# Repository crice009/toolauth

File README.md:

# toolauth

A simple server to handle integration of a tool authorization system with custom curcuit boards. 
Designed by and for use at MakeHaven in New Haven, CT.

## toolauth-hardware
The hardware is also custom. It can be referenced [here](https://github.com/crice009/toolauth-hardware).

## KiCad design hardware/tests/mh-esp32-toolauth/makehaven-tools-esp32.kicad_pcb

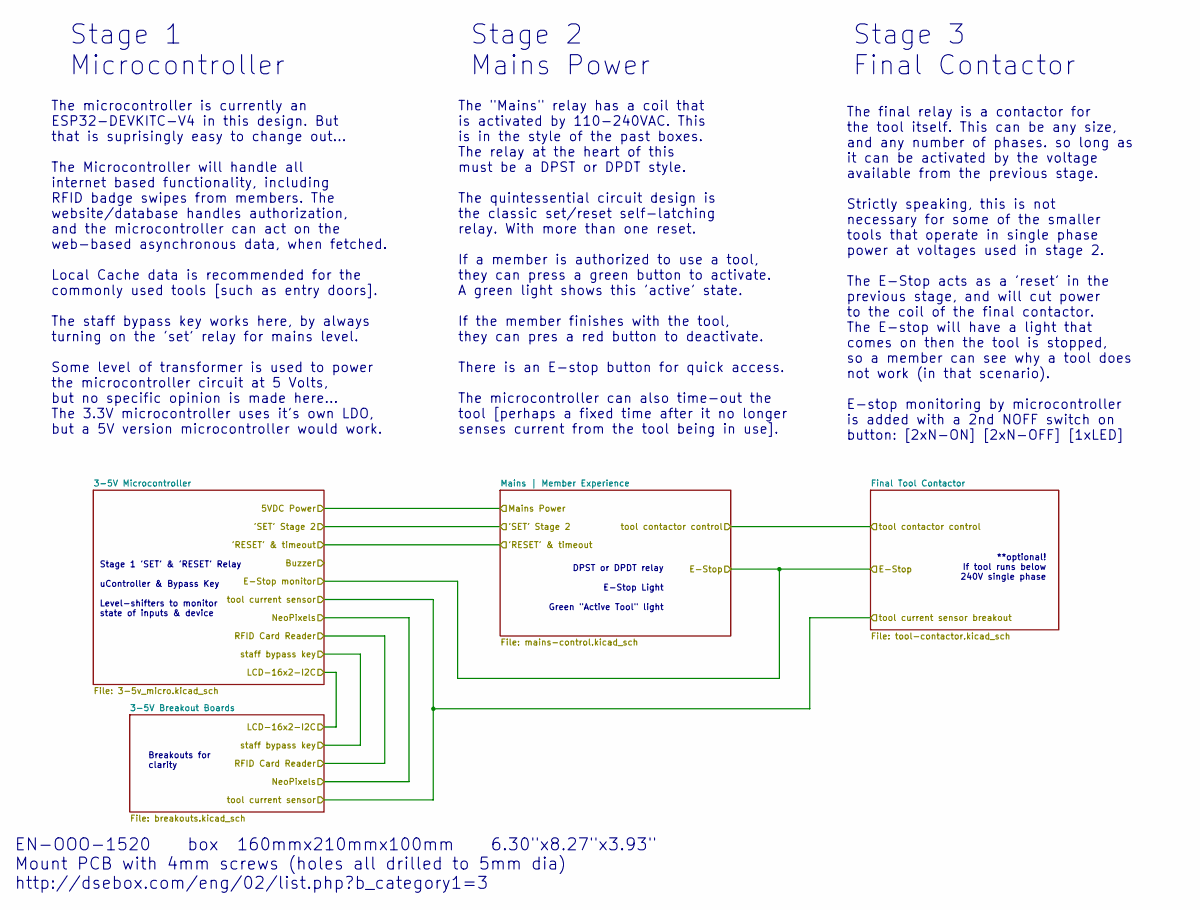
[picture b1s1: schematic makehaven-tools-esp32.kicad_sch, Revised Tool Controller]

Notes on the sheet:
Stage 3 Final Contactor
Stage 1 'SET' & 'RESET' Relay uController & Bypass Key Level-shifters to monitor state of inputs & device
The final relay is a contactor for the tool itself. This can be any size, and any number of phases. so long as it can be activated by the voltage available from the previous stage. Strictly speaking, this is not necessary for some of the smaller tools that operate in single phase power at voltages 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
Stage 2 Mains Power
Stage 1 Microcontroller
The "Mains" relay has a coil that is activated by 110-240VAC. This is in the style of the past boxes. The relay at the heart of this must be a DPST or DPDT style. The quintessential circuit design is the classic set/reset self-latching relay. With more than one reset. If a member is authorized to u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
**optional! If tool runs below 240V single phase
Breakouts for clarity
The microcontroller is currently an ESP32-DEVKITC-V4 in this design. But that is suprisingly easy to change out... The Microcontroller will handle all internet based functionality, including RFID badge swipes from members. The website/database handles authorization, and the microcontroller can act 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
DPST or DPDT relay E-Stop Light Green "Active Tool" light
EN-OOO-1520 box 160mmx210mmx100mm 6.30"x8.27"x3.93" Mount PCB with 4mm screws (holes all drilled to 5mm dia) http://dsebox.com/eng/02/list.php?b_category1=3

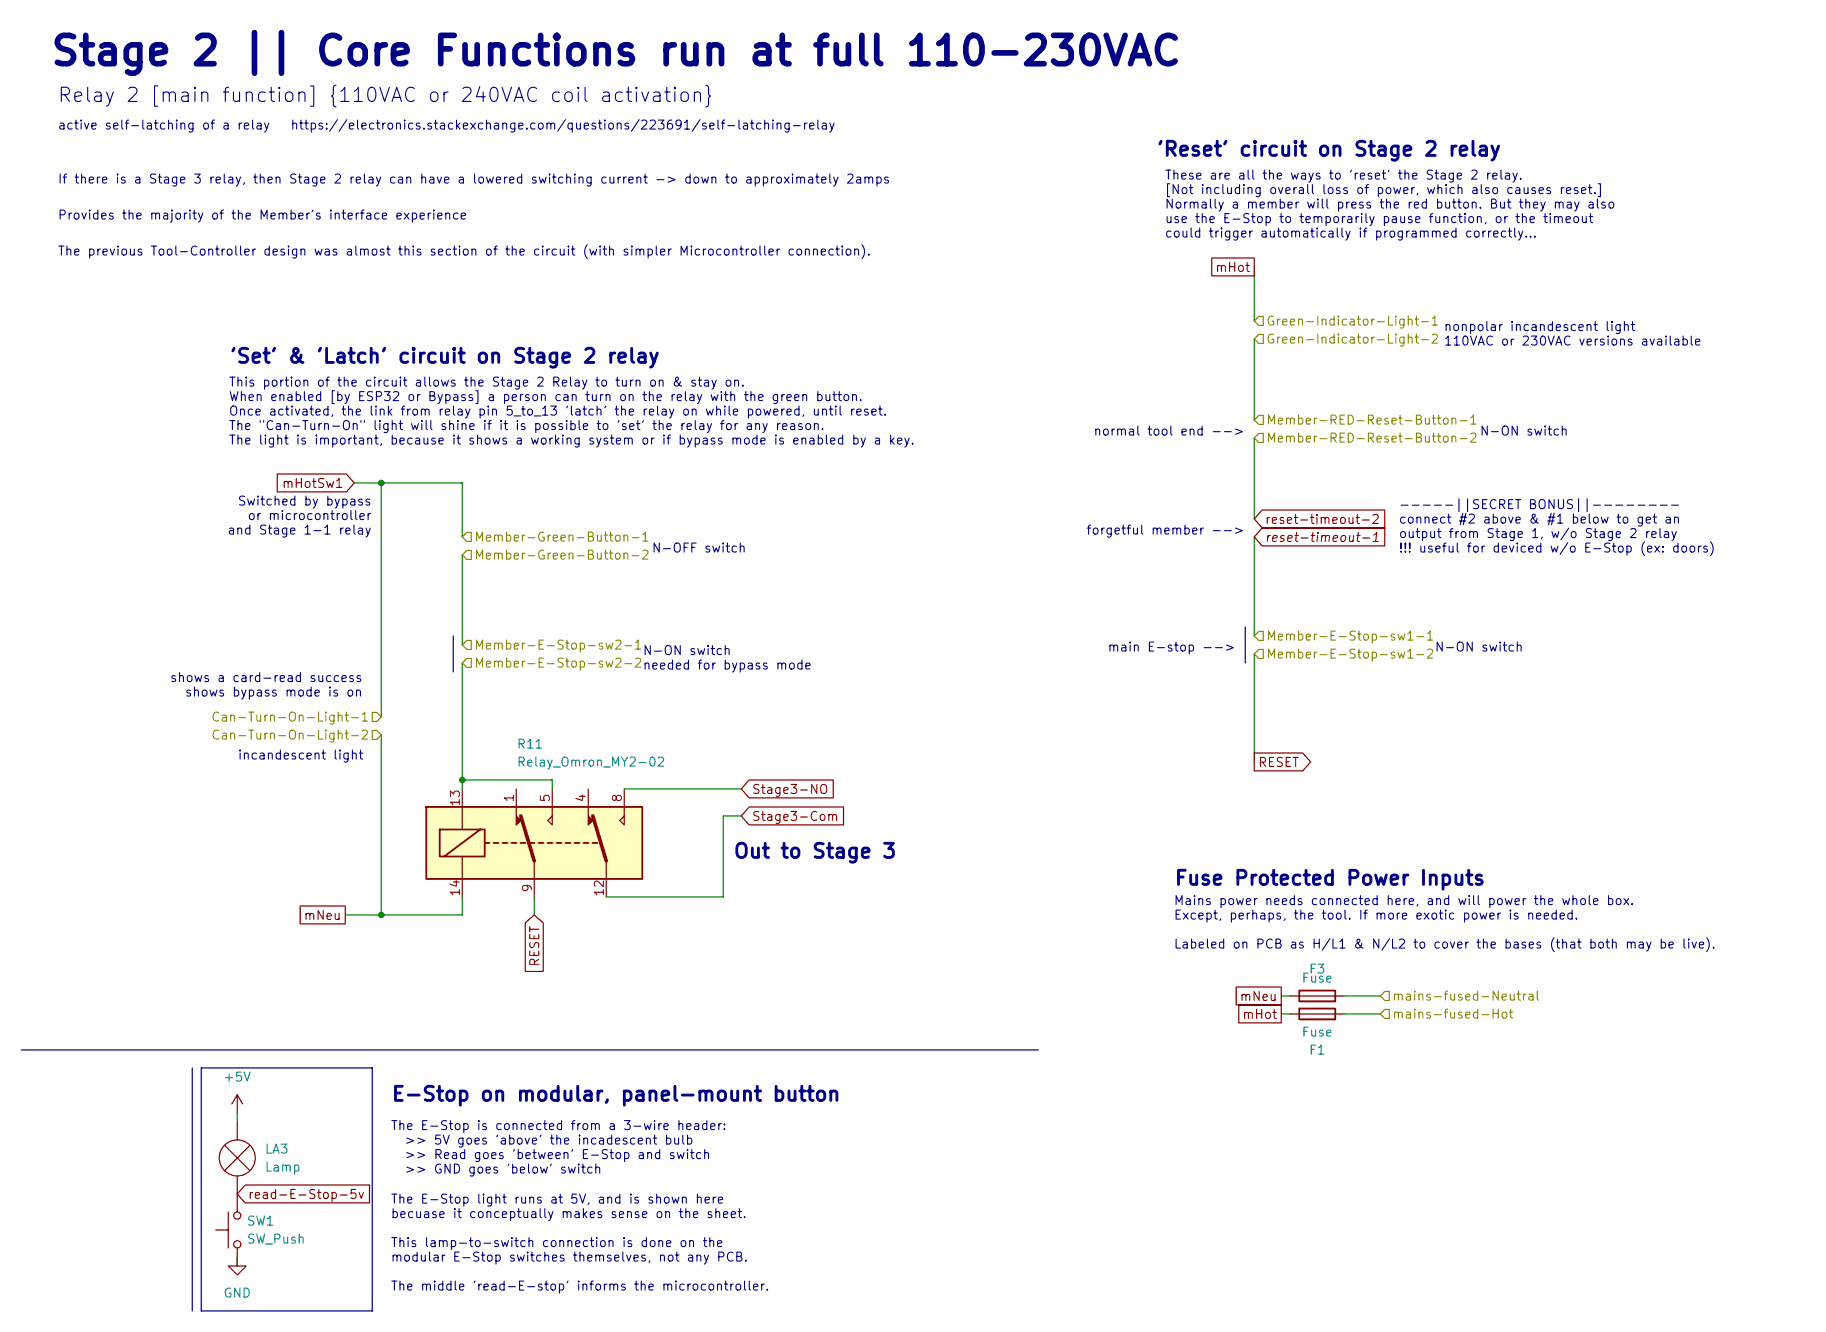
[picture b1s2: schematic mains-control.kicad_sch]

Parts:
F1, F3: Fuse; Fuseholder_Littelfuse_100_series_5x20mm
LA3: Lamp
R11: Relay_Omron_MY2-02; relay-Omron-MY2-02
SW1: SW_Push

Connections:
/Mains | Member Experience/Member-E-Stop-sw2-2: R11.5, R11.13; also elsewhere on the board
/Mains | Member Experience/mains-fused-Hot: F1.2; also elsewhere on the board
/Mains | Member Experience/mains-fused-Neutral: F3.2; also elsewhere on the board
unnamed: LA3.1 (-), SW1.2
RESET: R11.9; also elsewhere on the board
Stage3-Com: R11.12; also elsewhere on the board
mNeu: F3.1, R11.14; also elsewhere on the board

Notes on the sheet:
shows a card-read success shows bypass mode is on
'Set' & 'Latch' circuit on Stage 2 relay
Out to Stage 3
E-Stop on modular, panel-mount button
N-ON switch needed for bypass mode
This portion of the circuit allows the Stage 2 Relay to turn on & stay on. When enabled [by ESP32 or Bypass] a person can turn on the relay with the green button. Once activated, the link from relay pin 5_to_13 'latch' the relay on while powered, until reset. The "Can-Turn-On" light will shine if i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
incandescent light
N-ON switch
The previous Tool-Controller design was almost this section of the circuit (with simpler Microcontroller connection).
-----||SECRET BONUS||-------- connect #2 above & #1 below to get an output from Stage 1, w/o Stage 2 relay !!! useful for deviced w/o E-Stop (ex: doors)
Provides the majority of the Member's interface experience
active self-latching of a relay https://electronics.stackexchange.com/questions/223691/self-latching-relay
N-OFF switch
normal tool end -->
If there is a Stage 3 relay, then Stage 2 relay can have a lowered switching current -> down to approximately 2amps
These are all the ways to 'reset' the Stage 2 relay. [Not including overall loss of power, which also causes reset.] Normally a member will press the red button. But they may also use the E-Stop to temporarily pause function, or the timeout could trigger automatically if programmed correctly...
forgetful member -->
Mains power needs connected here, and will power the whole box. Except, perhaps, the tool. If more exotic power is needed. Labeled on PCB as H/L1 & N/L2 to cover the bases (that both may be live).
The E-Stop is connected from a 3-wire header: >> 5V goes 'above' the incadescent bulb >> Read goes 'between' E-Stop and switch >> GND goes 'below' switch
Relay 2 [main function] {110VAC or 240VAC coil activation}
'Reset' circuit on Stage 2 relay
The E-Stop light runs at 5V, and is shown here becuase it conceptually makes sense on the sheet. This lamp-to-switch connection is done on the modular E-Stop switches themselves, not any PCB. The middle 'read-E-stop' informs the microcontroller.
Switched by bypass or microcontroller and Stage 1-1 relay
main E-stop -->
Fuse Protected Power Inputs
nonpolar incandescent light 110VAC or 230VAC versions available
Stage 2 || Core Functions run at full 110-230VAC

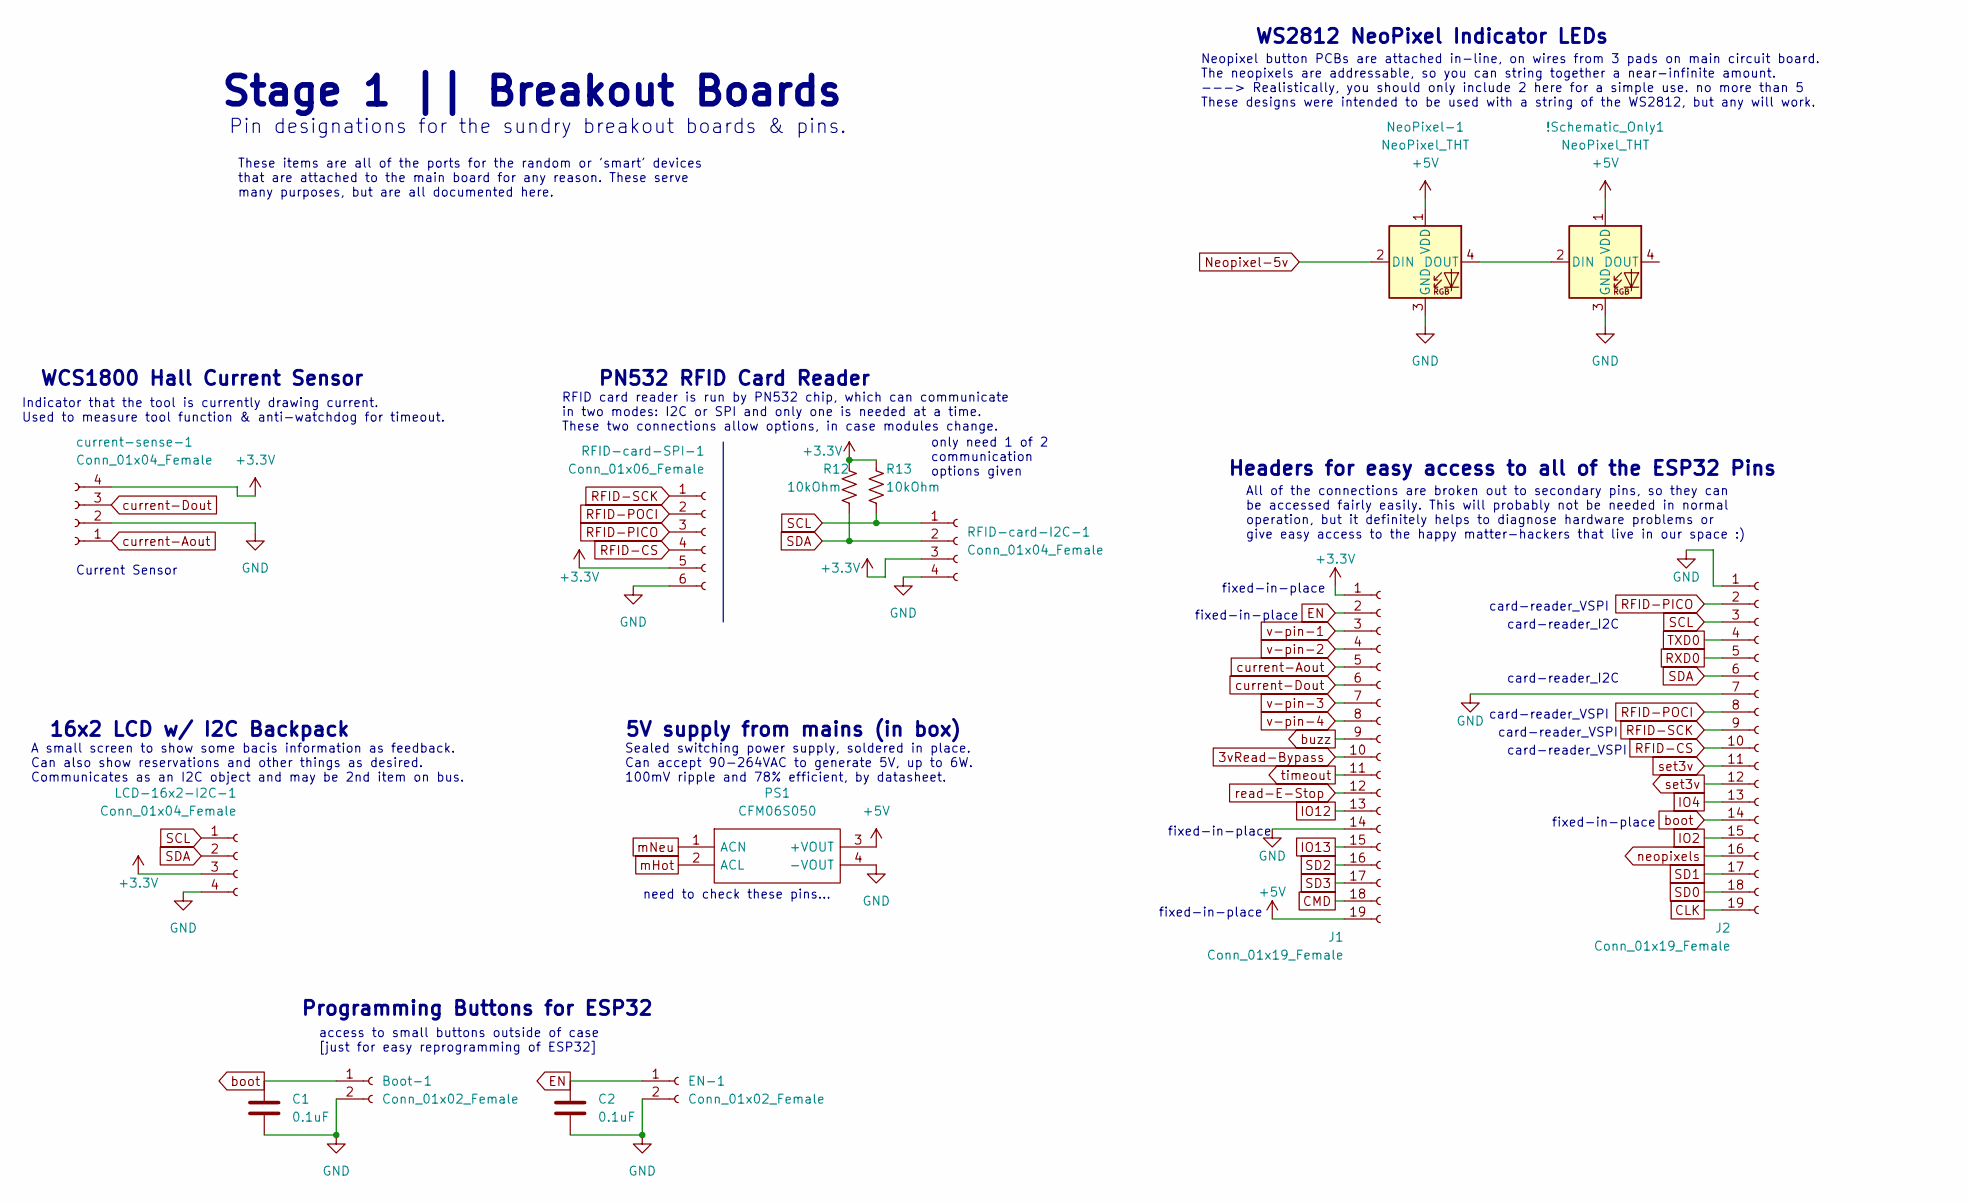
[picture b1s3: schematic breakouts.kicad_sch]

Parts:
!Schematic_Only1: NeoPixel_THT
Boot-1: Conn_01x02_Female; PinSocket_1x02_P2.54mm_Vertical
C1, C2: 0.1uF; C_1206_3216Metric_Pad1.33x1.80mm_HandSolder
EN-1: Conn_01x02_Female; PinSocket_1x02_P2.54mm_Vertical
J1, J2: Conn_01x19_Female; PinSocket_1x19_P2.54mm_Vertical
LCD-16x2-I2C-1: Conn_01x04_Female; PinSocket_1x04_P2.54mm_Vertical
NeoPixel-1: NeoPixel_THT; PinSocket_1x03_P2.54mm_Vertical
PS1: CFM06S050; Mouser Part Number 418-CFM06S050
R12, R13: 10kOhm; R_1206_3216Metric_Pad1.30x1.75mm_HandSolder
RFID-card-I2C-1: Conn_01x04_Female; PinSocket_1x04_P2.54mm_Vertical
RFID-card-SPI-1: Conn_01x06_Female; PinSocket_1x06_P2.54mm_Vertical
current-sense-1: Conn_01x04_Female; PinSocket_1x04_P2.54mm_Vertical

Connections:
3vRead-Bypass: J1.10; also elsewhere on the board
+3V3: J1.1, LCD-16x2-I2C-1.3, R12.2, R13.2, RFID-card-I2C-1.3, RFID-card-SPI-1.5, current-sense-1.4; also elsewhere on the board
+5V: !Schematic_Only1.1 (VDD), J1.19, NeoPixel-1.1 (VDD), PS1.3 (+VOUT); also elsewhere on the board
CLK: J2.19; also elsewhere on the board
CMD: J1.18; also elsewhere on the board
EN: C2.1, EN-1.1, J1.2; also elsewhere on the board
GND: !Schematic_Only1.3 (GND), Boot-1.2, C1.2, C2.2, EN-1.2, J1.14, J2.1, J2.7, LCD-16x2-I2C-1.4, NeoPixel-1.3 (GND), PS1.4 (-VOUT), RFID-card-I2C-1.4, RFID-card-SPI-1.6, current-sense-1.2; also elsewhere on the board
IO2: J2.15; also elsewhere on the board
IO4: J2.13; also elsewhere on the board
IO12: J1.13; also elsewhere on the board
IO13: J1.15; also elsewhere on the board
Neopixel-5v: NeoPixel-1.2 (DIN); also elsewhere on the board
unnamed: !Schematic_Only1.2 (DIN), NeoPixel-1.4 (DOUT)
RFID-CS: J2.10, RFID-card-SPI-1.4; also elsewhere on the board
RFID-PICO: J2.2, RFID-card-SPI-1.3; also elsewhere on the board
RFID-POCI: J2.8, RFID-card-SPI-1.2; also elsewhere on the board
RFID-SCK: J2.9, RFID-card-SPI-1.1; also elsewhere on the board
RXD0: J2.5; also elsewhere on the board
SCL: J2.3, LCD-16x2-I2C-1.1, R13.1, RFID-card-I2C-1.1; also elsewhere on the board
SD0: J2.18; also elsewhere on the board
SD1: J2.17; also elsewhere on the board
SD2: J1.16; also elsewhere on the board
SD3: J1.17; also elsewhere on the board
SDA: J2.6, LCD-16x2-I2C-1.2, R12.1, RFID-card-I2C-1.2; also elsewhere on the board
TXD0: J2.4; also elsewhere on the board
boot: Boot-1.1, C1.1, J2.14; also elsewhere on the board
buzz: J1.9; also elsewhere on the board
current-Aout: J1.5, current-sense-1.1; also elsewhere on the board
current-Dout: J1.6, current-sense-1.3; also elsewhere on the board
mNeu: PS1.1 (ACN); also elsewhere on the board
neopixels: J2.16; also elsewhere on the board
read-E-Stop: J1.12; also elsewhere on the board
set3v: J2.11, J2.12; also elsewhere on the board
timeout: J1.11; also elsewhere on the board
v-pin-1: J1.3; also elsewhere on the board
v-pin-2: J1.4; also elsewhere on the board
v-pin-3: J1.7; also elsewhere on the board
v-pin-4: J1.8; also elsewhere on the board

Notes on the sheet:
access to small buttons outside of case [just for easy reprogramming of ESP32]
Headers for easy access to all of the ESP32 Pins
need to check these pins...
PN532 RFID Card Reader
A small screen to show some bacis information as feedback. Can also show reservations and other things as desired. Communicates as an I2C object and may be 2nd item on bus.
card-reader_VSPI
Neopixel button PCBs are attached in-line, on wires from 3 pads on main circuit board. The neopixels are addressable, so you can string together a near-infinite amount. ---> Realistically, you should only include 2 here for a simple use. no more than 5 These designs were intended to be used with a 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
Sealed switching power supply, soldered in place. Can accept 90-264VAC to generate 5V, up to 6W. 100mV ripple and 78% efficient, by datasheet.
These items are all of the ports for the random or 'smart' devices that are attached to the main board for any reason. These serve many purposes, but are all documented here.
fixed-in-place
Current Sensor
Indicator that the tool is currently drawing current. Used to measure tool function & anti-watchdog for timeout.
16x2 LCD w/ I2C Backpack
Programming Buttons for ESP32
Pin designations for the sundry breakout boards & pins.
Stage 1 || Breakout Boards
RFID card reader is run by PN532 chip, which can communicate in two modes: I2C or SPI and only one is needed at a time. These two connections allow options, in case modules change.
card-reader_I2C
All of the connections are broken out to secondary pins, so they can be accessed fairly easily. This will probably not be needed in normal operation, but it definitely helps to diagnose hardware problems or give easy access to the happy matter-hackers that live in our space :)
WS2812 NeoPixel Indicator LEDs
WCS1800 Hall Current Sensor
5V supply from mains (in box)
only need 1 of 2 communication options given

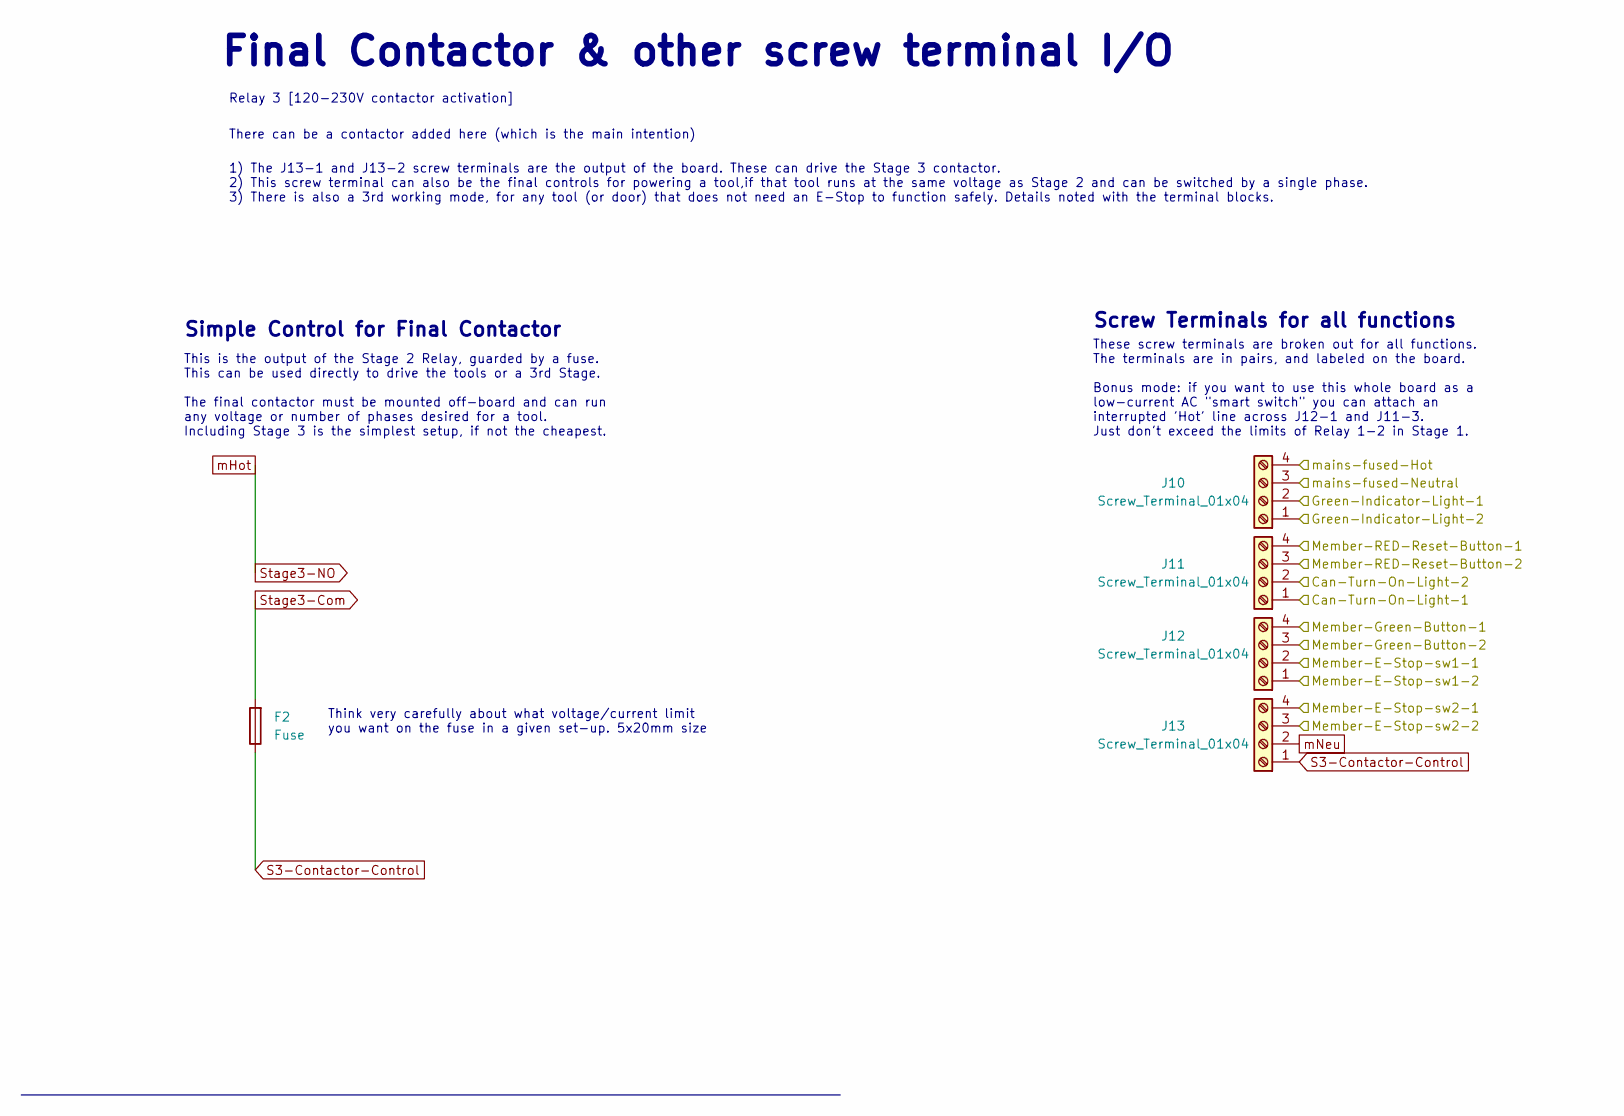
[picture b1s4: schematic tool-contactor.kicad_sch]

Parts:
F2: Fuse; Fuseholder_Littelfuse_100_series_5x20mm
J10, J11, J12, J13: Screw_Terminal_01x04; TerminalBlock_Altech_AK300-4_P5.00mm

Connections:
/Mains | Member Experience/Green-Indicator-Light-2: J10.1, J11.4
/Mains | Member Experience/Member-E-Stop-sw2-1: J12.3, J13.4
/Mains | Member Experience/Member-E-Stop-sw2-2: J13.3; also elsewhere on the board
/Mains | Member Experience/mains-fused-Hot: J10.4; also elsewhere on the board
/Mains | Member Experience/mains-fused-Neutral: J10.3; also elsewhere on the board
RESET: J12.1; also elsewhere on the board
S3-Contactor-Control: F2.1, J13.1
Stage3-Com: F2.2; also elsewhere on the board
mHotSw1: J11.1, J12.4; also elsewhere on the board
mNeu: J11.2, J13.2; also elsewhere on the board
reset-timeout-1: J12.2; also elsewhere on the board
reset-timeout-2: J11.3; also elsewhere on the board

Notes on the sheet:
Final Contactor & other screw terminal I/O
Screw Terminals for all functions
Relay 3 [120-230V contactor activation]
These screw terminals are broken out for all functions. The terminals are in pairs, and labeled on the board. Bonus mode: if you want to use this whole board as a low-current AC "smart switch" you can attach an interrupted 'Hot' line across J12-1 and J11-3. Just don't exceed the limits of Relay 1-2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
Simple Control for Final Contactor
1) The J13-1 and J13-2 screw terminals are the output of the board. These can drive the Stage 3 contactor. 2) This screw terminal can also be the final controls for powering a tool,if that tool runs at the same voltage as Stage 2 and can be switched by a single phase. 3) There is also a 3rd working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
Think very carefully about what voltage/current limit you want on the fuse in a given set-up. 5x20mm size
This is the output of the Stage 2 Relay, guarded by a fuse. This can be used directly to drive the tools or a 3rd Stage. The final contactor must be mounted off-board and can run any voltage or number of phases desired for a tool. Including Stage 3 is the simplest setup, if not the cheapest.
There can be a contactor added here (which is the main intention)

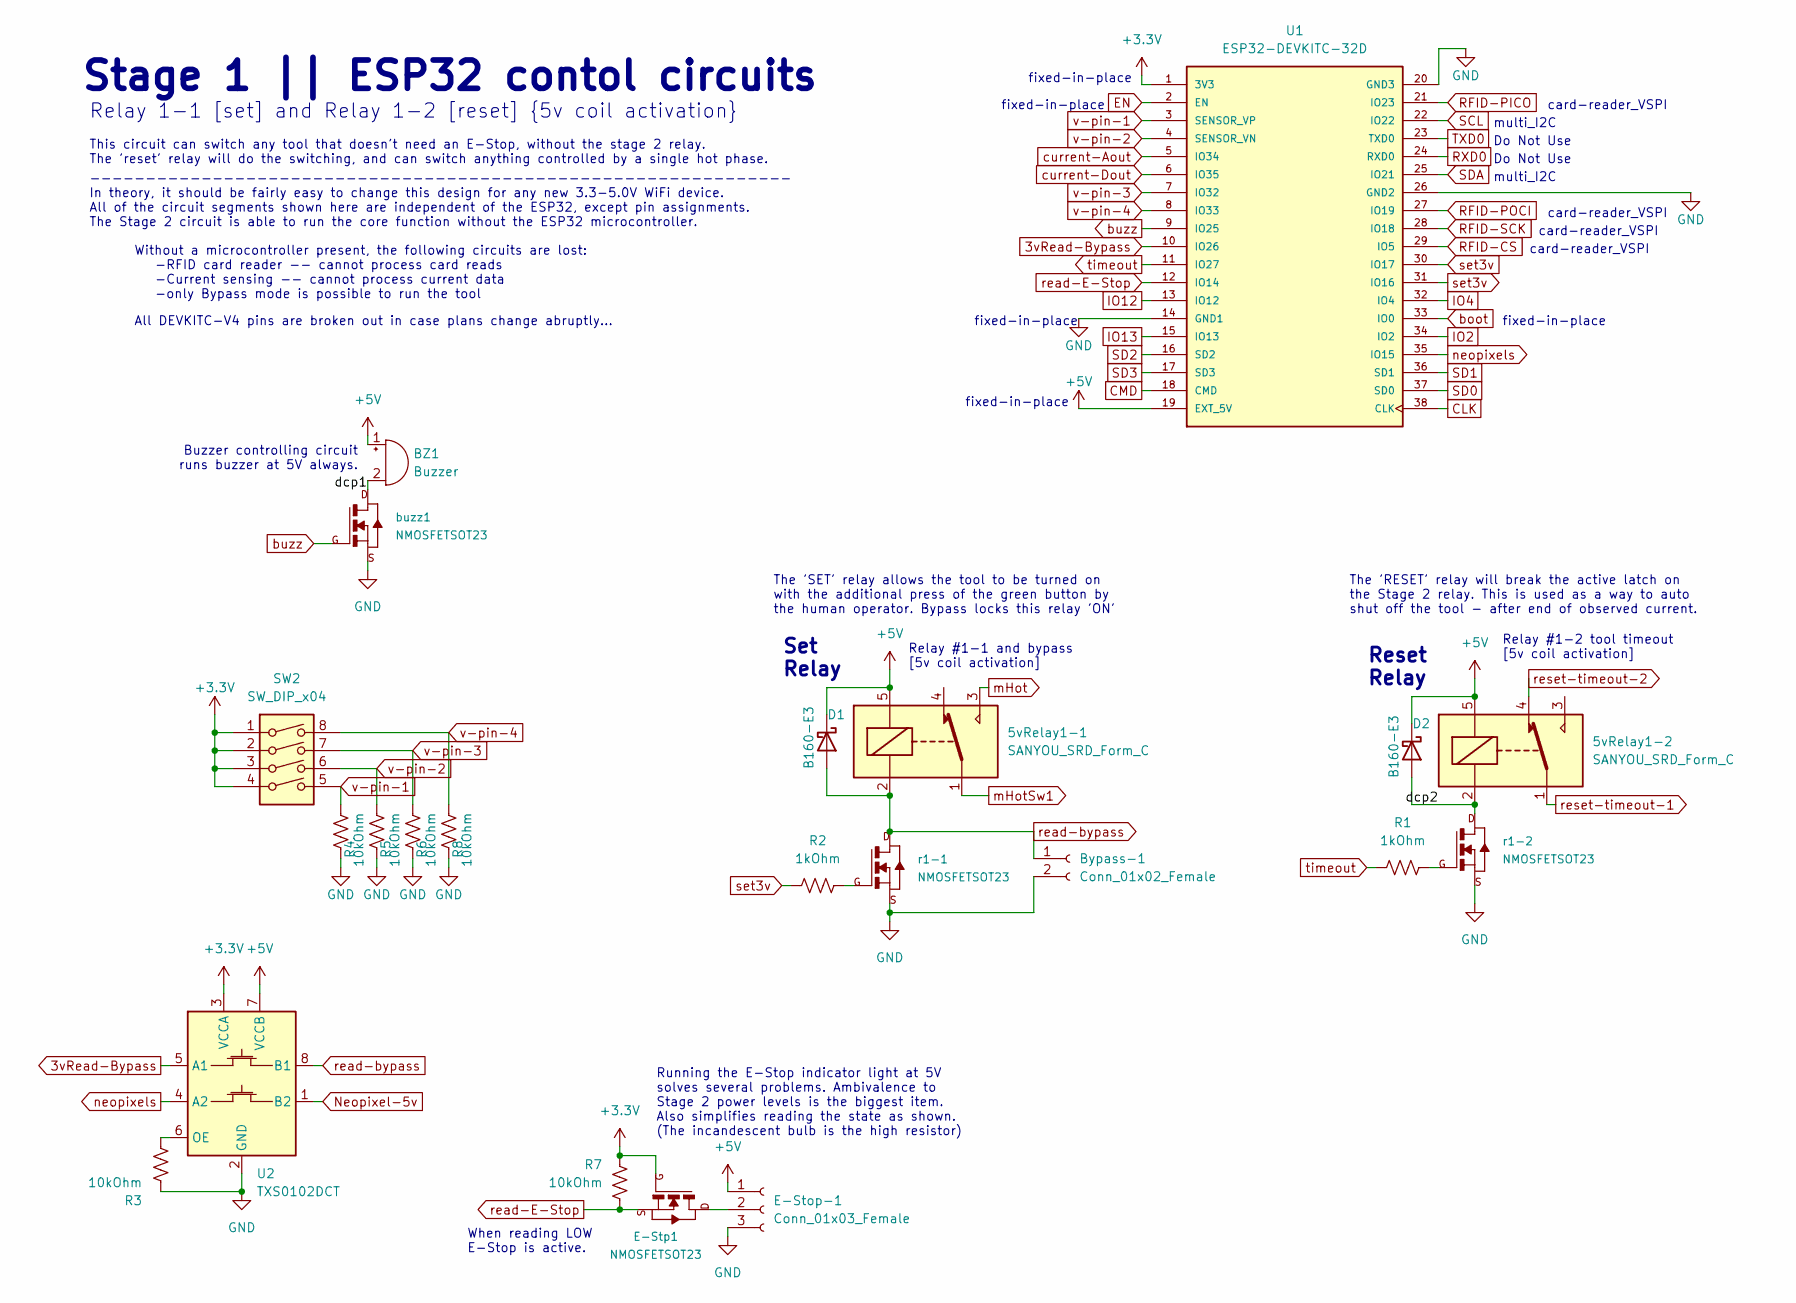
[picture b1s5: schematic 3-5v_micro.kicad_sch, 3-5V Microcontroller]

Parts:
5vRelay1-1, 5vRelay1-2: SANYOU_SRD_Form_C; Relay_SPDT_SANYOU_SRD_Series_Form_C
BZ1: Buzzer; Buzzer_15x7.5RM7.6
Bypass-1: Conn_01x02_Female; PinSocket_1x02_P2.54mm_Vertical
D1, D2: B160-E3; D_SMA
E-Stop-1: Conn_01x03_Female; PinSocket_1x03_P2.54mm_Vertical
E-Stp1: NMOSFETSOT23; SOT-23
R1, R2: 1kOhm; R_1206_3216Metric_Pad1.30x1.75mm_HandSolder
R3, R4, R5, R6, R7, R8: 10kOhm; R_1206_3216Metric_Pad1.30x1.75mm_HandSolder
SW2: SW_DIP_x04; SW_DIP_SPSTx04_Slide_6.7x11.72mm_W7.62mm_P2.54mm_LowProfile
U1: ESP32-DEVKITC-32D; MODULE_ESP32-DEVKITC-32D; PARTREV 4
U2: TXS0102DCT; SSOP-8_2.95x2.8mm_P0.65mm
buzz1: NMOSFETSOT23; SOT-23
r1-1, r1-2: NMOSFETSOT23; SOT-23

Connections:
3vRead-Bypass: U1.10 (IO26), U2.5 (A1); also elsewhere on the board
+3V3: E-Stp1.3 (G), R7.2, SW2.1, SW2.2, SW2.3, SW2.4, U1.1 (3V3), U2.3 (VCCA); also elsewhere on the board
+5V: 5vRelay1-1.5, 5vRelay1-2.5, BZ1.1 (-), D1.1 (K), D2.1 (K), E-Stop-1.1, U1.19 (EXT_5V), U2.7 (VCCB); also elsewhere on the board
/3-5V Microcontroller/dcp1: BZ1.2 (+), buzz1.1 (D)
/3-5V Microcontroller/dcp2: 5vRelay1-2.2, D2.2 (A), r1-2.1 (D)
CLK: U1.38 (CLK); also elsewhere on the board
CMD: U1.18 (CMD); also elsewhere on the board
EN: U1.2 (EN); also elsewhere on the board
GND: Bypass-1.2, E-Stop-1.3, R3.2, R4.1, R5.1, R6.1, R8.1, U1.14 (GND1), U1.20 (GND3), U1.26 (GND2), U2.2 (GND), buzz1.2 (S), r1-1.2 (S), r1-2.2 (S); also elsewhere on the board
IO2: U1.34 (IO2); also elsewhere on the board
IO4: U1.32 (IO4); also elsewhere on the board
IO12: U1.13 (IO12); also elsewhere on the board
IO13: U1.15 (IO13); also elsewhere on the board
Neopixel-5v: U2.1 (B2); also elsewhere on the board
unnamed: E-Stop-1.2, E-Stp1.1 (D)
unnamed: R1.2, r1-2.3 (G)
unnamed: R2.2, r1-1.3 (G)
unnamed: R3.1, U2.6 (OE)
RFID-CS: U1.29 (IO5); also elsewhere on the board
RFID-PICO: U1.21 (IO23); also elsewhere on the board
RFID-POCI: U1.27 (IO19); also elsewhere on the board
RFID-SCK: U1.28 (IO18); also elsewhere on the board
RXD0: U1.24 (RXD0); also elsewhere on the board
SCL: U1.22 (IO22); also elsewhere on the board
SD0: U1.37 (SD0); also elsewhere on the board
SD1: U1.36 (SD1); also elsewhere on the board
SD2: U1.16 (SD2); also elsewhere on the board
SD3: U1.17 (SD3); also elsewhere on the board
SDA: U1.25 (IO21); also elsewhere on the board
TXD0: U1.23 (TXD0); also elsewhere on the board
boot: U1.33 (IO0); also elsewhere on the board
buzz: U1.9 (IO25), buzz1.3 (G); also elsewhere on the board
current-Aout: U1.5 (IO34); also elsewhere on the board
current-Dout: U1.6 (IO35); also elsewhere on the board
mHotSw1: 5vRelay1-1.1; also elsewhere on the board
neopixels: U1.35 (IO15), U2.4 (A2); also elsewhere on the board
read-E-Stop: E-Stp1.2 (S), R7.1, U1.12 (IO14); also elsewhere on the board
read-bypass: 5vRelay1-1.2, Bypass-1.1, D1.2 (A), U2.8 (B1), r1-1.1 (D)
reset-timeout-1: 5vRelay1-2.1; also elsewhere on the board
reset-timeout-2: 5vRelay1-2.4; also elsewhere on the board
set3v: R2.1, U1.30 (IO17), U1.31 (IO16); also elsewhere on the board
timeout: R1.1, U1.11 (IO27); also elsewhere on the board
v-pin-1: R4.2, SW2.5, U1.3 (SENSOR_VP); also elsewhere on the board
v-pin-2: R5.2, SW2.6, U1.4 (SENSOR_VN); also elsewhere on the board
v-pin-3: R6.2, SW2.7, U1.7 (IO32); also elsewhere on the board
v-pin-4: R8.2, SW2.8, U1.8 (IO33); also elsewhere on the board

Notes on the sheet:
Running the E-Stop indicator light at 5V solves several problems. Ambivalence to Stage 2 power levels is the biggest item. Also simplifies reading the state as shown. (The incandescent bulb is the high resistor)
The 'RESET' relay will break the active latch on the Stage 2 relay. This is used as a way to auto shut off the tool - after end of observed current.
Reset Relay
fixed-in-place
All DEVKITC-V4 pins are broken out in case plans change abruptly...
Do Not Use
card-reader_VSPI
Stage 1 || ESP32 contol circuits
Relay 1-1 [set] and Relay 1-2 [reset] {5v coil activation}
When reading LOW E-Stop is active.
Set Relay
The 'SET' relay allows the tool to be turned on with the additional press of the green button by the human operator. Bypass locks this relay 'ON'
This circuit can switch any tool that doesn't need an E-Stop, without the stage 2 relay. The 'reset' relay will do the switching, and can switch anything controlled by a single hot phase.
multi_I2C
Without a microcontroller present, the following circuits are lost: -RFID card reader -- cannot process card reads -Current sensing -- cannot process current data -only Bypass mode is possible to run the tool
Relay #1-2 tool timeout [5v coil activation]
--------------------------------------------------------------- In theory, it should be fairly easy to change this design for any new 3.3-5.0V WiFi device. All of the circuit segments shown here are independent of the ESP32, except pin assignments. The Stage 2 circuit is able to run the core functi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
Buzzer controlling circuit runs buzzer at 5V always.
Relay #1-1 and bypass [5v coil activation]

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
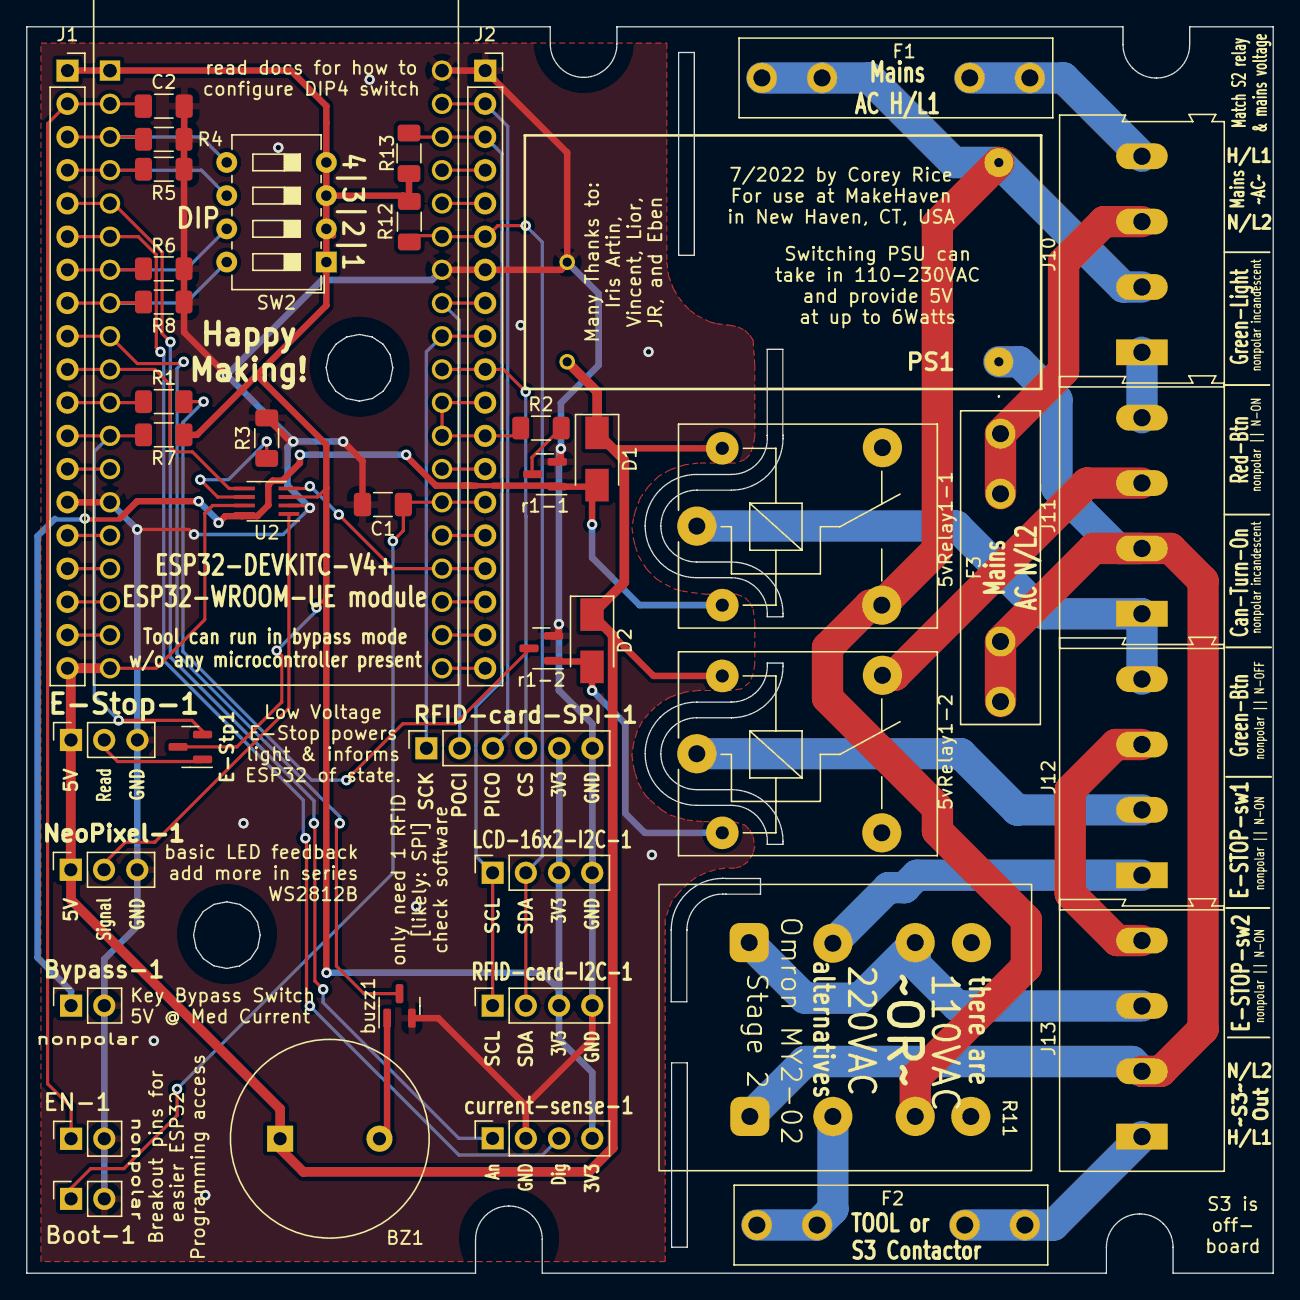
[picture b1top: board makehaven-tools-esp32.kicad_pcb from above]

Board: 2 copper layers, 95.4 x 95.4 mm, 44 parts (0 on the bottom side), 56 nets.
